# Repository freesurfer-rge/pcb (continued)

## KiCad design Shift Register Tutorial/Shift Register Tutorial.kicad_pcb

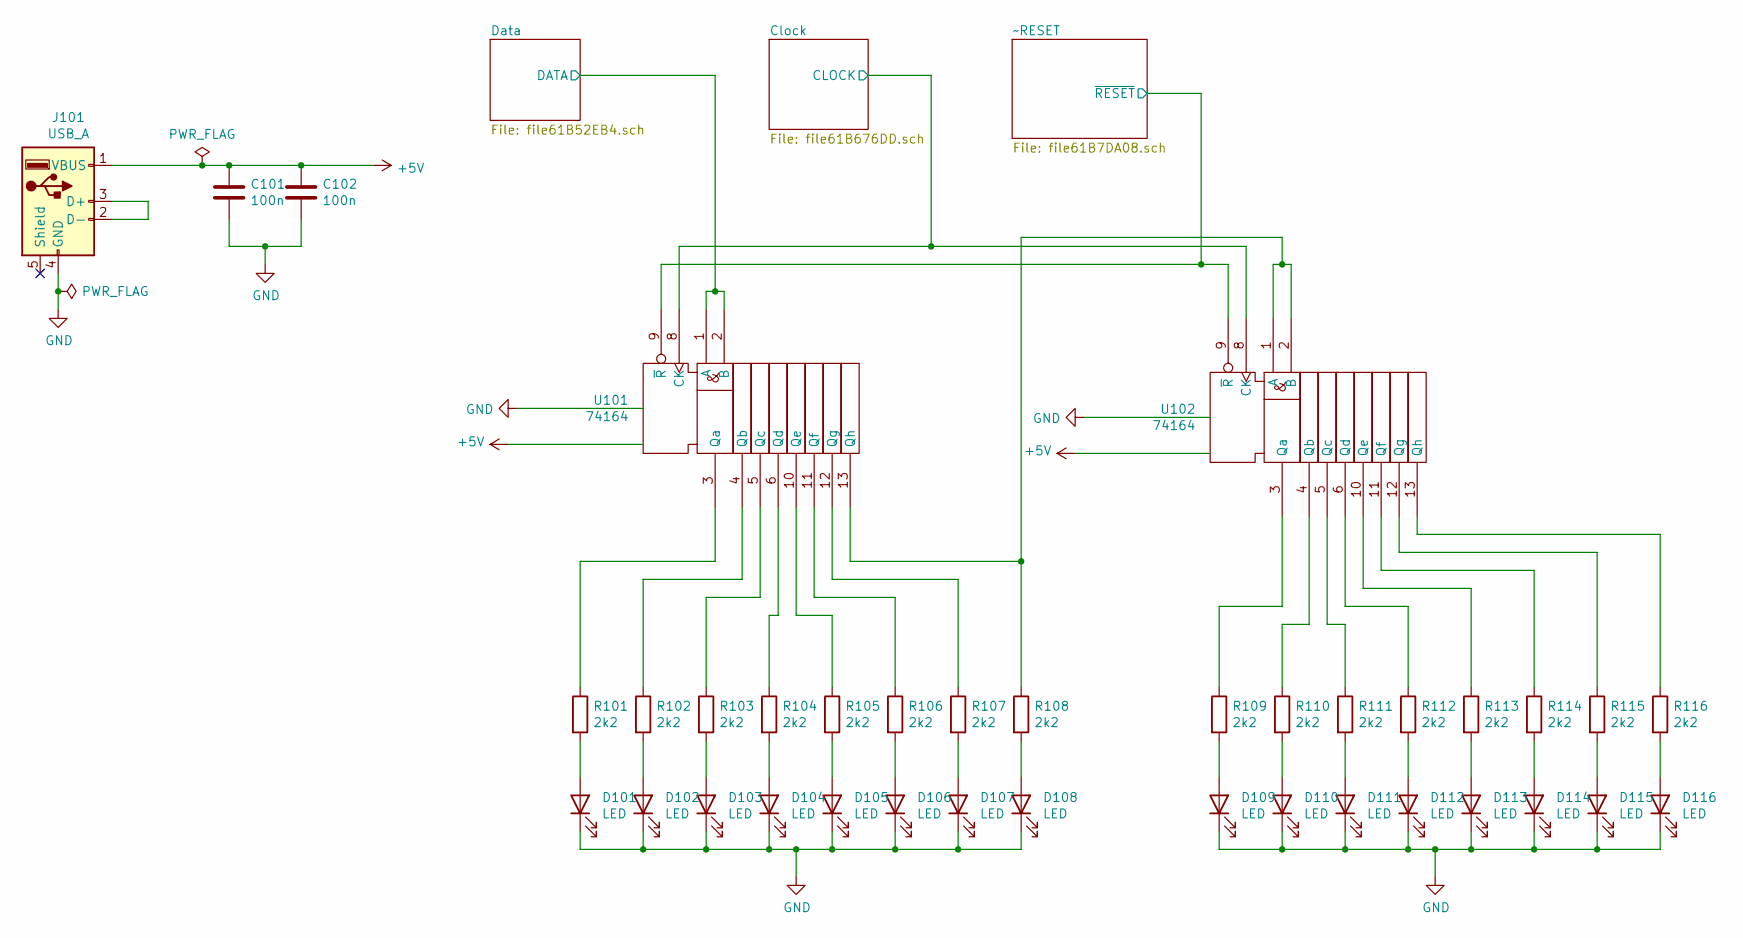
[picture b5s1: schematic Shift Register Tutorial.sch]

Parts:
C101, C102: 100n; C_Disc_D4.7mm_W2.5mm_P5.00mm
D101, D102, D103, D104, D105, D106, D107, D108, D109, D110, D111, D112, D113, D114, D115, D116: LED; LED_D5.0mm
J101: USB_A; USB_A_Molex_67643_Horizontal
R101, R102, R103, R104, R105, R106, R107, R108, R109, R110, R111, R112, R113, R114, R115, R116: 2k2; R_Axial_DIN0207_L6.3mm_D2.5mm_P7.62mm_Horizontal
U101, U102: 74164; DIP-14_W7.62mm_Socket

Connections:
+5V: C101.2, C102.2, J101.1 (VBUS), U101.14 (Vdd), U102.14 (Vdd); also elsewhere on the board
/Clock/CLOCK: U101.8 (CK), U102.8 (CK); also elsewhere on the board
/Data/DATA: U101.1 (A), U101.2 (B); also elsewhere on the board
/~RESET/~RESET: U101.9 (~R), U102.9 (~R); also elsewhere on the board
GND: C101.1, C102.1, D101.1 (K), D102.1 (K), D103.1 (K), D104.1 (K), D105.1 (K), D106.1 (K), D107.1 (K), D108.1 (K), D109.1 (K), D110.1 (K), D111.1 (K), D112.1 (K), D113.1 (K), D114.1 (K), D115.1 (K), D116.1 (K), J101.4 (GND), U101.7 (Vss), U102.7 (Vss); also elsewhere on the board
unnamed: D101.2 (A), R101.2
unnamed: D102.2 (A), R102.2
unnamed: D103.2 (A), R103.2
unnamed: D104.2 (A), R104.2
unnamed: D105.2 (A), R105.2
unnamed: D106.2 (A), R106.2
unnamed: D107.2 (A), R107.2
unnamed: D108.2 (A), R108.2
unnamed: D109.2 (A), R109.2
unnamed: D110.2 (A), R110.2
unnamed: D111.2 (A), R111.2
unnamed: D112.2 (A), R112.2
unnamed: D113.2 (A), R113.2
unnamed: D114.2 (A), R114.2
unnamed: D115.2 (A), R115.2
unnamed: D116.2 (A), R116.2
unnamed: J101.2 (D-), J101.3 (D+)
unnamed: R101.1, U101.3 (Qa)
unnamed: R102.1, U101.4 (Qb)
unnamed: R103.1, U101.5 (Qc)
unnamed: R104.1, U101.6 (Qd)
unnamed: R105.1, U101.10 (Qe)
unnamed: R106.1, U101.11 (Qf)
unnamed: R107.1, U101.12 (Qg)
unnamed: R108.1, U101.13 (Qh), U102.1 (A), U102.2 (B)
unnamed: R109.1, U102.3 (Qa)
unnamed: R110.1, U102.4 (Qb)
unnamed: R111.1, U102.5 (Qc)
unnamed: R112.1, U102.6 (Qd)
unnamed: R113.1, U102.10 (Qe)
unnamed: R114.1, U102.11 (Qf)
unnamed: R115.1, U102.12 (Qg)
unnamed: R116.1, U102.13 (Qh)

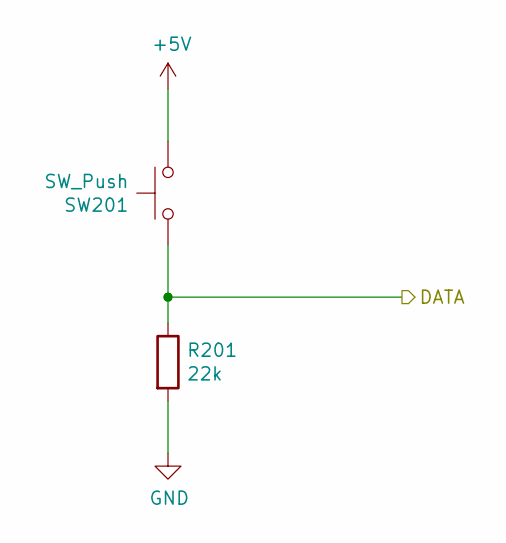
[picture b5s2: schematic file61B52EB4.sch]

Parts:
R201: 22k; R_Axial_DIN0207_L6.3mm_D2.5mm_P7.62mm_Horizontal
SW201: SW_Push; SW_PUSH_6mm_H4.3mm

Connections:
+5V: SW201.2; also elsewhere on the board
/Data/DATA: R201.1, SW201.1; also elsewhere on the board
GND: R201.2; also elsewhere on the board

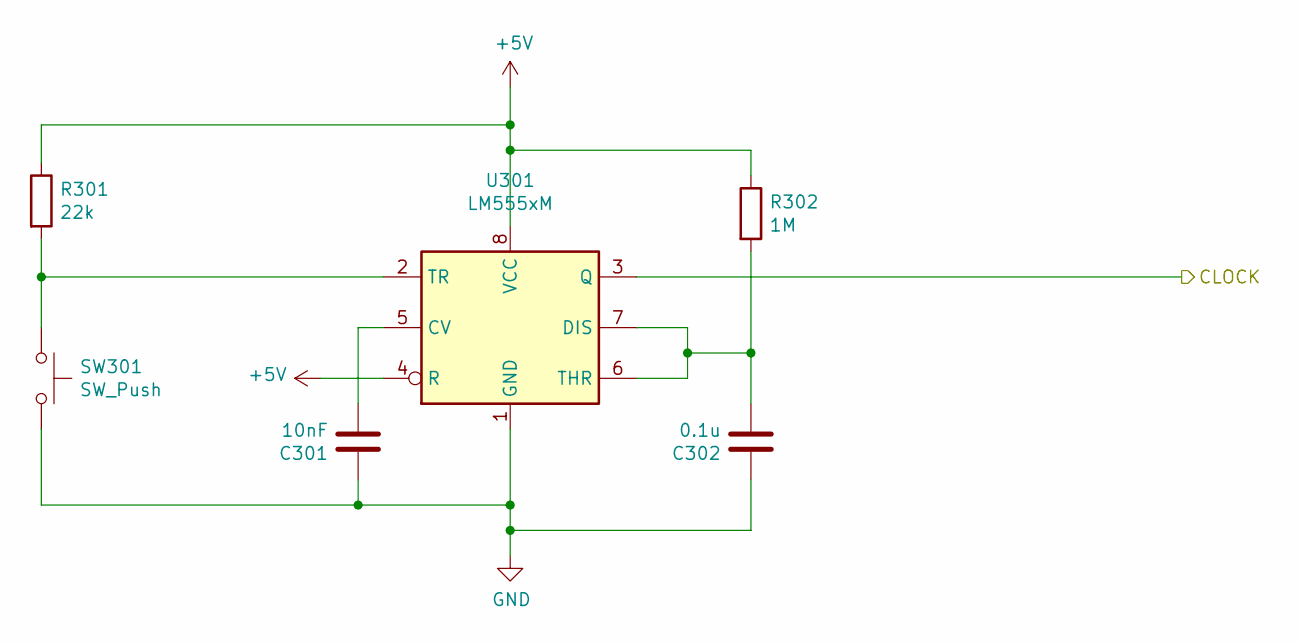
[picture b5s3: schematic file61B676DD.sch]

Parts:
C301: 10nF; C_Disc_D3.0mm_W2.0mm_P2.50mm
C302: 0.1u; C_Disc_D4.7mm_W2.5mm_P5.00mm
R301: 22k; R_Axial_DIN0207_L6.3mm_D2.5mm_P7.62mm_Horizontal
R302: 1M; R_Axial_DIN0207_L6.3mm_D2.5mm_P7.62mm_Horizontal
SW301: SW_Push; SW_PUSH_6mm_H4.3mm
U301: LM555xM; DIP-8_W7.62mm_Socket

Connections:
+5V: R301.1, R302.1, U301.4 (R), U301.8 (VCC); also elsewhere on the board
/Clock/CLOCK: U301.3 (Q); also elsewhere on the board
GND: C301.2, C302.1, SW301.2, U301.1 (GND); also elsewhere on the board
unnamed: C301.1, U301.5 (CV)
unnamed: C302.2, R302.2, U301.6 (THR), U301.7 (DIS)
unnamed: R301.2, SW301.1, U301.2 (TR)

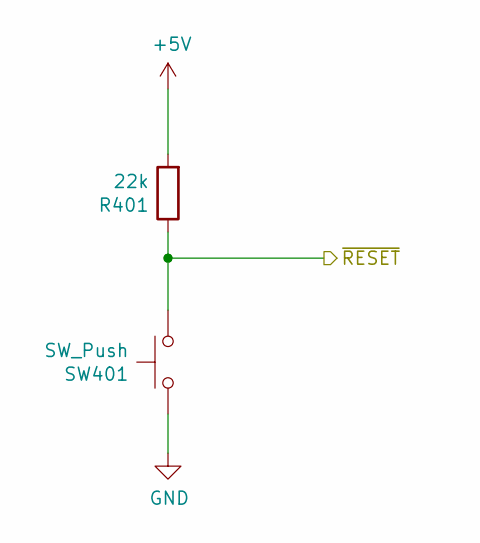
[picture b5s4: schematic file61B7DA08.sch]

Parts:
R401: 22k; R_Axial_DIN0207_L6.3mm_D2.5mm_P7.62mm_Horizontal
SW401: SW_Push; SW_PUSH_6mm_H4.3mm

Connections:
+5V: R401.2; also elsewhere on the board
/~RESET/~RESET: R401.1, SW401.2; also elsewhere on the board
GND: SW401.1; also elsewhere on the board

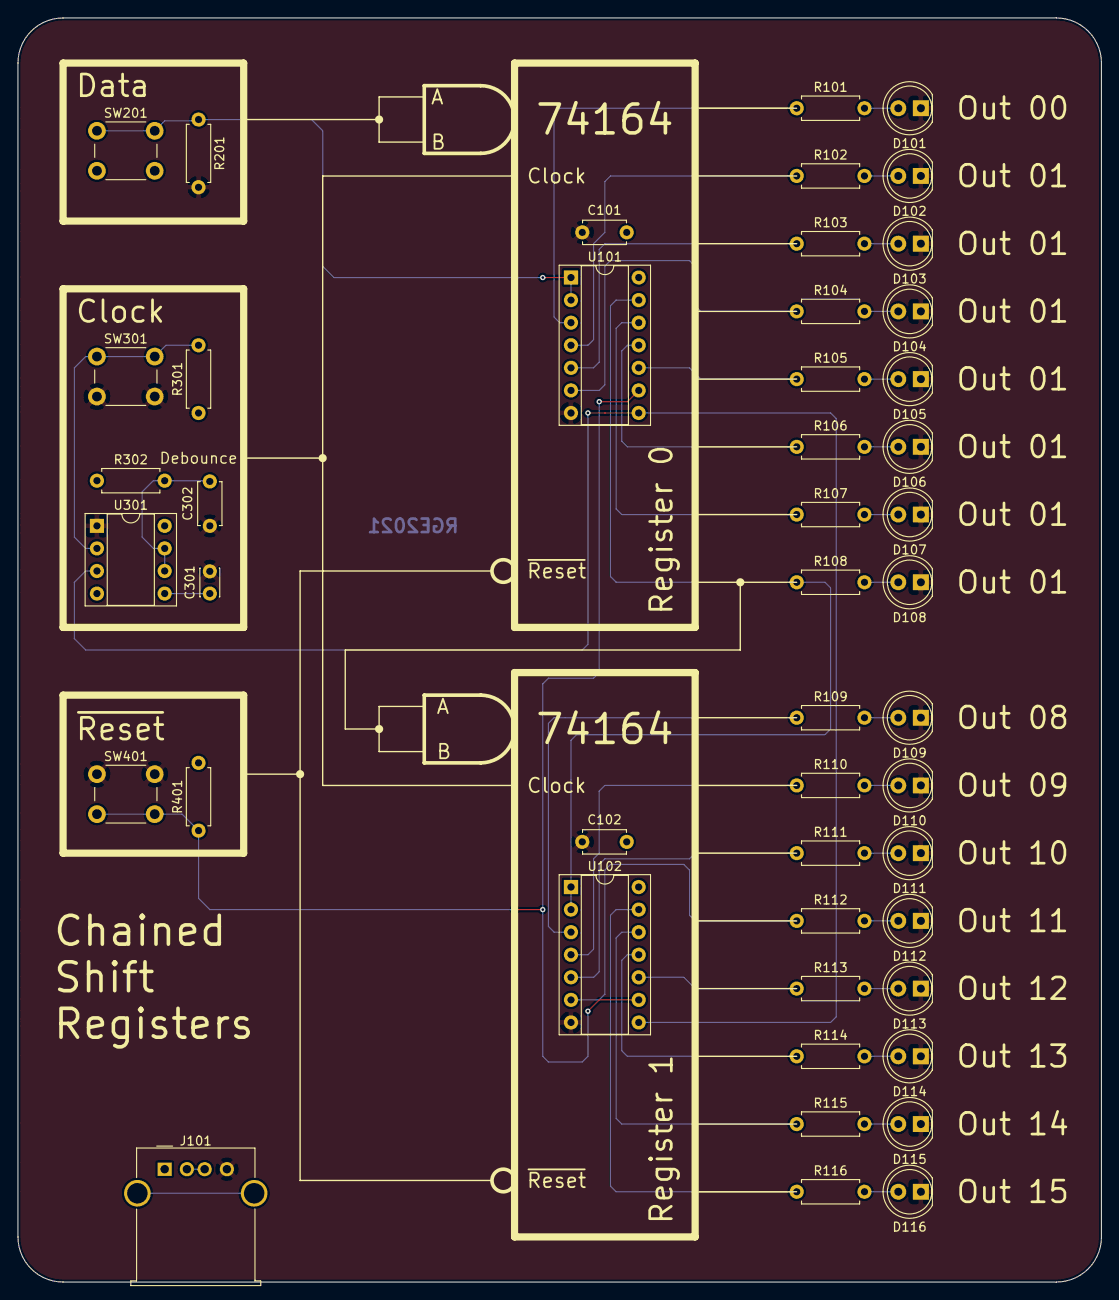
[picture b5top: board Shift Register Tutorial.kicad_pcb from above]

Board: 2 copper layers, 121.9 x 142.2 mm, 47 parts (0 on the bottom side), 41 nets.

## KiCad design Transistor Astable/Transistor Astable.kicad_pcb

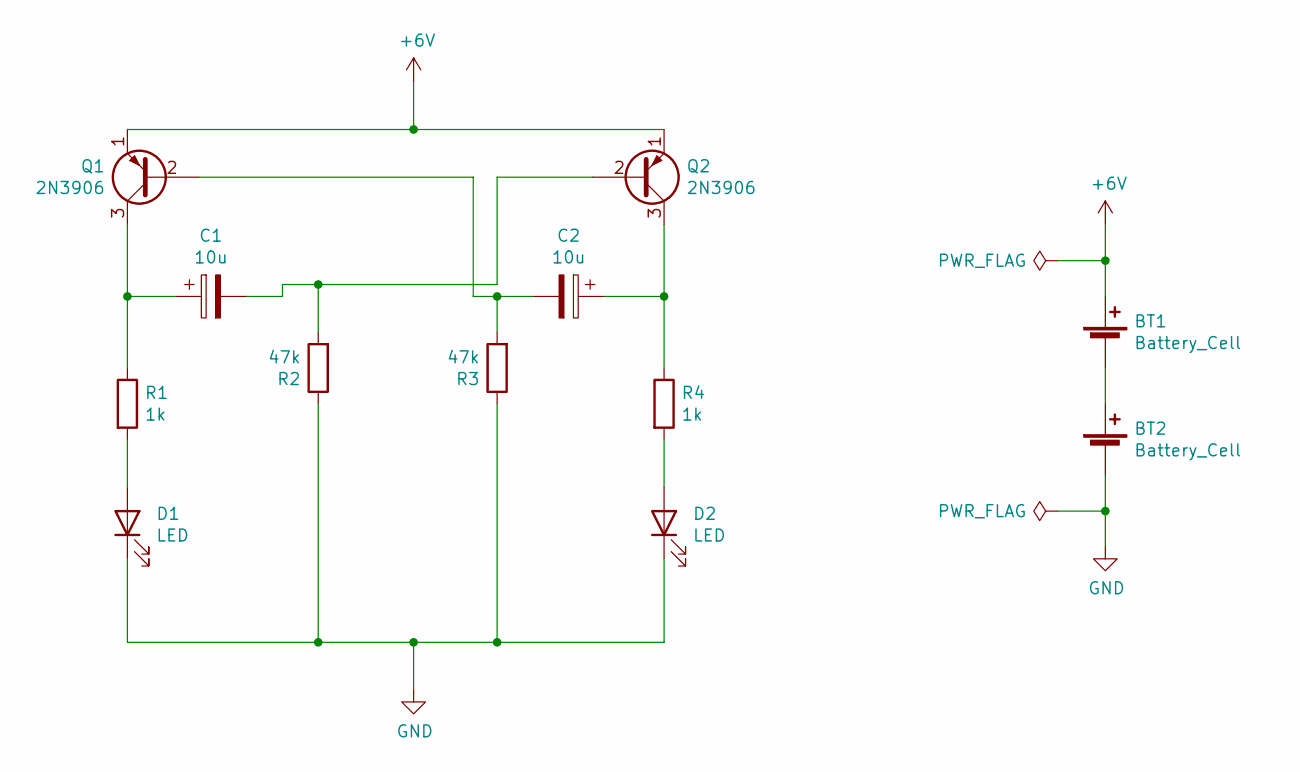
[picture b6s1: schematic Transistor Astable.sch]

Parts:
BT1, BT2: Battery_Cell; BattHold_Linx_CR2032
C1, C2: 10u; CP_Radial_D4.0mm_P2.00mm
D1, D2: LED; LED_D5.0mm
Q1, Q2: 2N3906; TO-92_Inline_Wide
R1, R4: 1k; R_Axial_DIN0207_L6.3mm_D2.5mm_P7.62mm_Horizontal
R2, R3: 47k; R_Axial_DIN0207_L6.3mm_D2.5mm_P7.62mm_Horizontal

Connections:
+6V: BT1.1 (+), Q1.1 (E), Q2.1 (E)
GND: BT2.2 (-), D1.1 (K), D2.1 (K), R2.1, R3.1
unnamed: BT1.2 (-), BT2.1 (+)
unnamed: C1.1, Q1.3 (C), R1.1
unnamed: C1.2, Q2.2 (B), R2.2
unnamed: C2.1, Q2.3 (C), R4.1
unnamed: C2.2, Q1.2 (B), R3.2
unnamed: D1.2 (A), R1.2
unnamed: D2.2 (A), R4.2

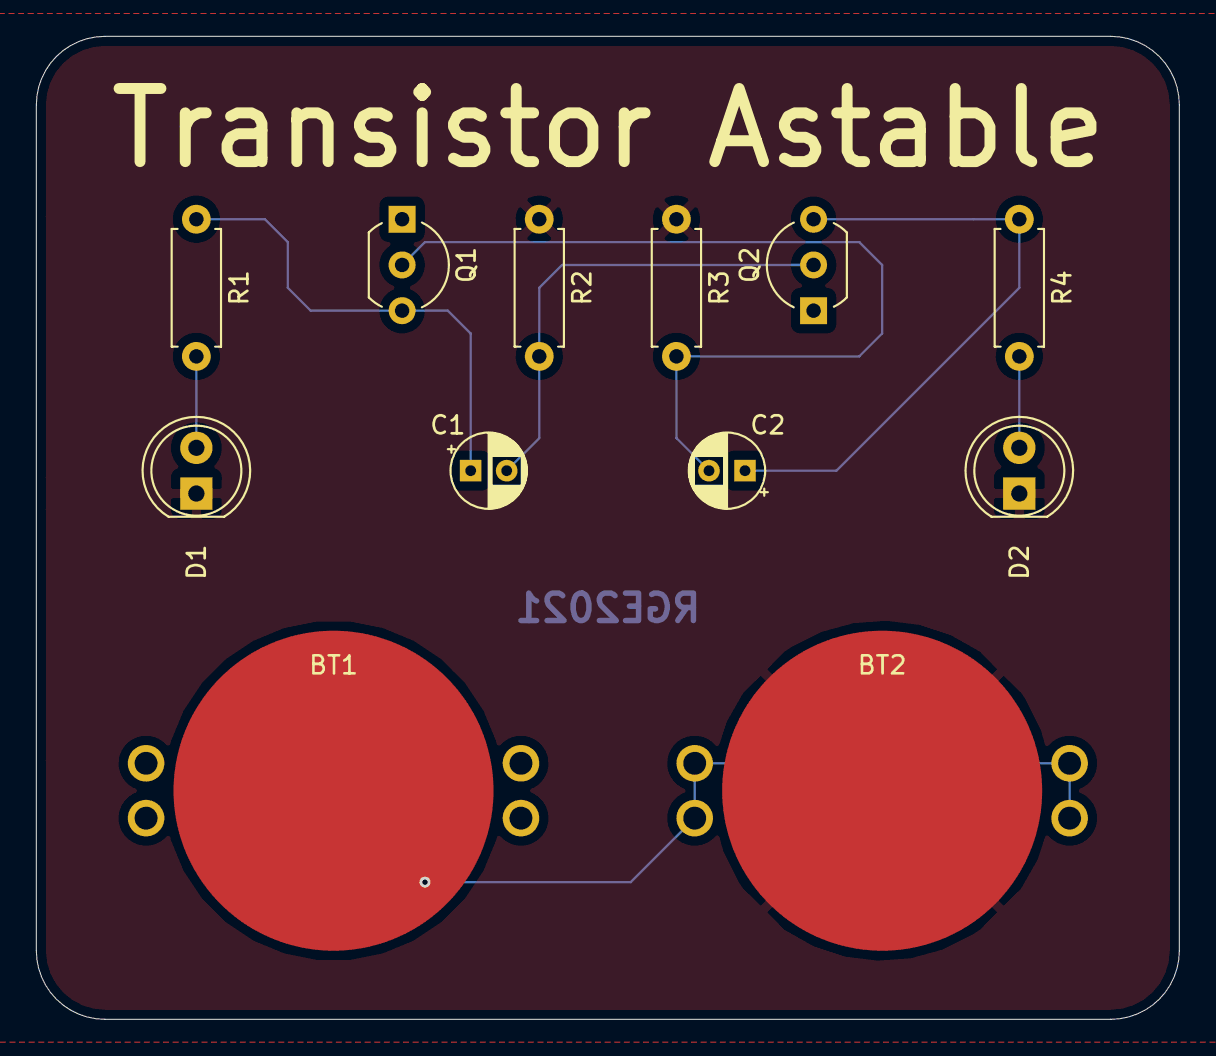
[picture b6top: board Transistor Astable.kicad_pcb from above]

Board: 2 copper layers, 63.5 x 54.6 mm, 12 parts (0 on the bottom side), 9 nets.

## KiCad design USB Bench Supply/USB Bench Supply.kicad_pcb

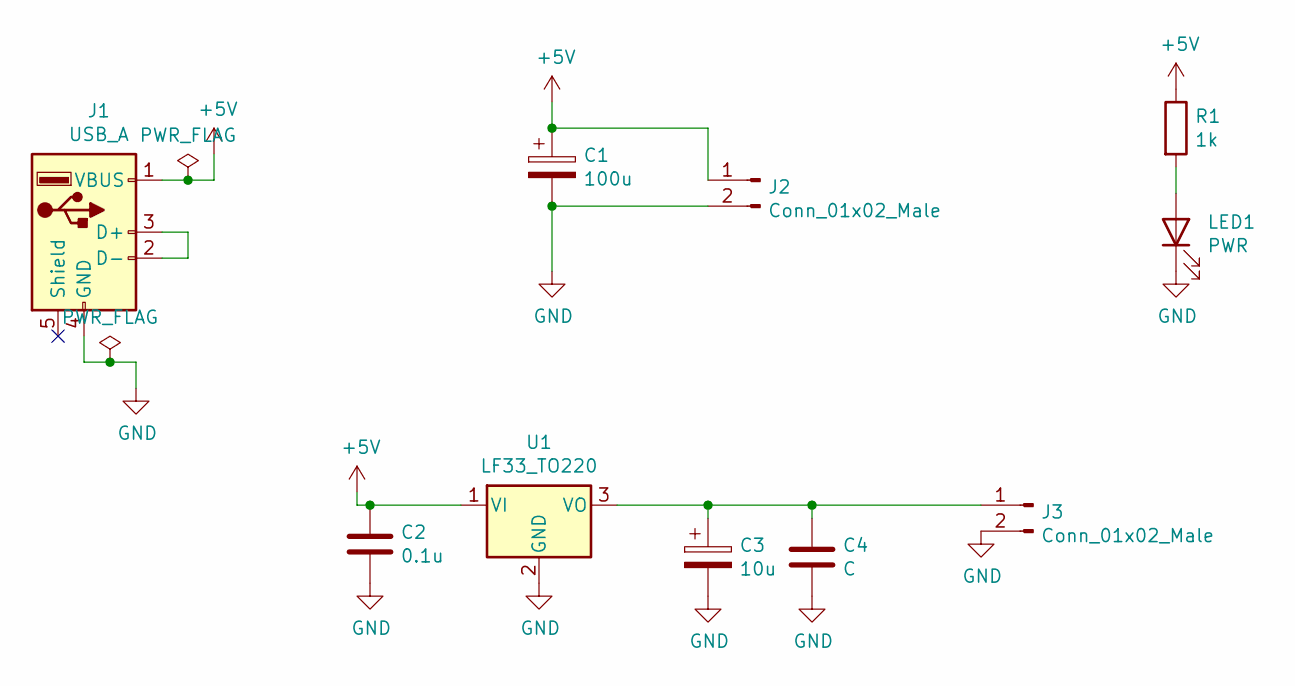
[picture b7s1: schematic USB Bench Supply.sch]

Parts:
C1: 100u; CP_Radial_D4.0mm_P1.50mm
C2: 0.1u; C_Disc_D5.0mm_W2.5mm_P5.00mm
C3: 10u; CP_Radial_D4.0mm_P1.50mm
C4: C; C_Disc_D4.7mm_W2.5mm_P5.00mm
J1: USB_A; USB_A_CONNFLY_DS1095-WNR0
J2, J3: Conn_01x02_Male; PinHeader_2x01_P2.54mm_Vertical
LED1: PWR; LED_D5.0mm
R1: 1k; R_Axial_DIN0207_L6.3mm_D2.5mm_P10.16mm_Horizontal
U1: LF33_TO220; TO-220-3_Horizontal_TabDown

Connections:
+5V: C1.1, C2.1, J1.1 (VBUS), J2.1, R1.1, U1.1 (VI)
GND: C1.2, C2.2, C3.2, C4.2, J1.4 (GND), J2.2, J3.2, LED1.1 (K), U1.2 (GND)
unnamed: C3.1, C4.1, J3.1, U1.3 (VO)
unnamed: J1.2 (D-), J1.3 (D+)
unnamed: LED1.2 (A), R1.2

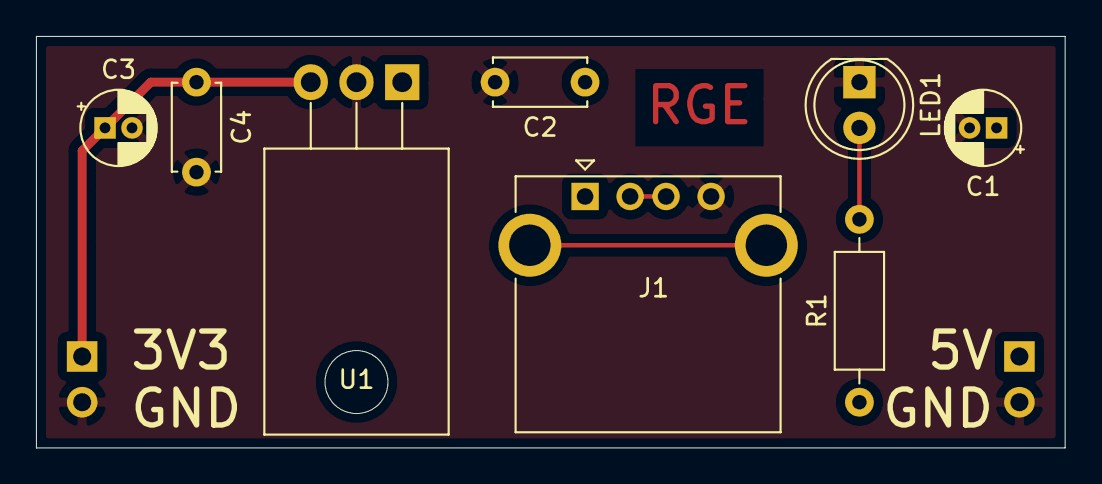
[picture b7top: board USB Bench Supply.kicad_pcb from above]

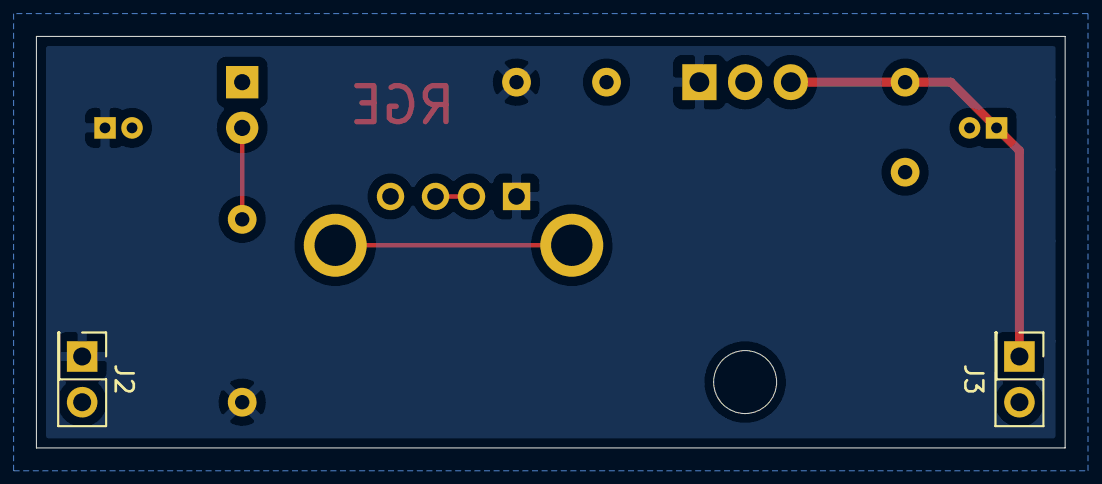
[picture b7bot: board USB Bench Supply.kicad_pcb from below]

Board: 2 copper layers, 57.2 x 22.9 mm, 10 parts (2 on the bottom side), 5 nets.
